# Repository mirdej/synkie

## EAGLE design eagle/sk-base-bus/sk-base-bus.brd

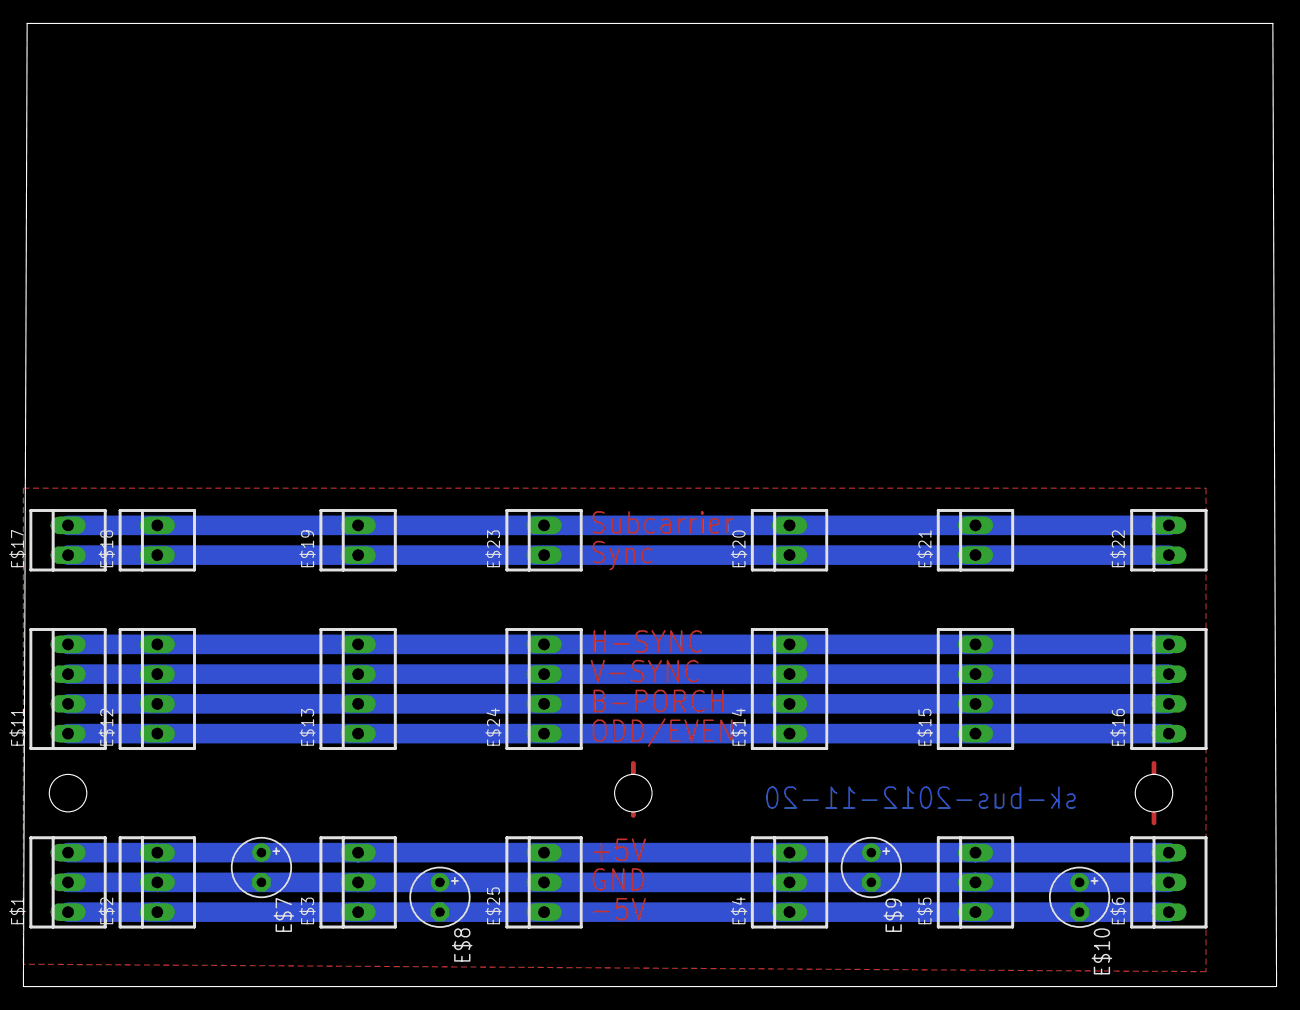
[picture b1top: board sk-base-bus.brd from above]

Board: 2 copper layers, 107.0 x 82.2 mm, 25 parts (0 on the bottom side), 9 nets.

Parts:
E$1, E$2, E$3, E$4, E$5, E$6, E$25: 22-23-2031
E$7, E$8, E$9, E$10: E2,5-5
E$11, E$12, E$13, E$14, E$15, E$16, E$24: 22-23-2041
E$17, E$18, E$19, E$20, E$21, E$22, E$23: 22-23-2021

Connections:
AGND: E$17.2, E$18.2, E$19.2, E$20.2, E$21.2, E$22.2
GND: E$1.2, E$2.2, E$3.2, E$4.2, E$5.2, E$6.2
S$1: E$1.3, E$2.3, E$3.3, E$4.3, E$5.3, E$6.3
S$3: E$1.1, E$2.1, E$3.1, E$4.1, E$5.1, E$6.1
S$5: E$11.4, E$12.4, E$13.4, E$14.4, E$15.4, E$16.4
S$6: E$11.3, E$12.3, E$13.3, E$14.3, E$15.3, E$16.3
S$7: E$11.2, E$12.2, E$13.2, E$14.2, E$15.2, E$16.2
S$8: E$11.1, E$12.1, E$13.1, E$14.1, E$15.1, E$16.1
S$10: E$17.1, E$18.1, E$19.1, E$20.1, E$21.1, E$22.1

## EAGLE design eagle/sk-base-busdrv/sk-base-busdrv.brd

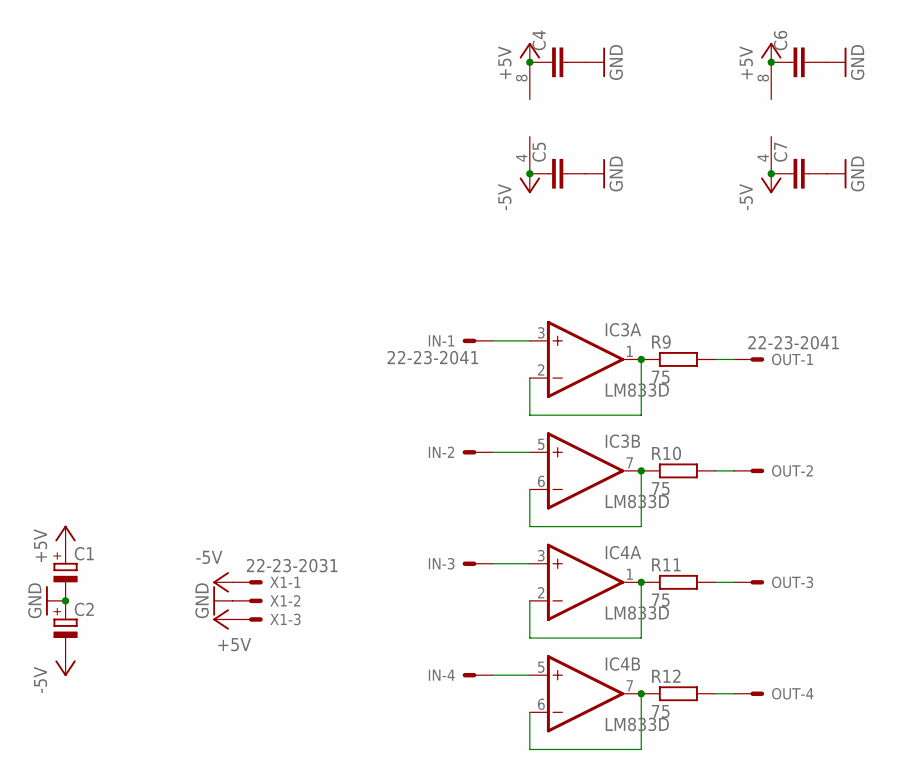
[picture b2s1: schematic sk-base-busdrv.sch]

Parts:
C1, C2: CPOL-EUCT6032; CT6032
C4, C5, C6, C7: C-EUC1206; C1206
IC3, IC4: LM833D; SO08
IN: 22-23-2041
OUT: 22-23-2041
R9, R10, R11, R12: 75; R1206
X1: 22-23-2031

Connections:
+5V: C1.+, C4.1, C6.1, IC3.8 (V+), IC4.8 (V+), X1.3
-5V: C2.-, C5.1, C7.1, IC3.4 (V-), IC4.4 (V-), X1.1
GND: C1.-, C2.+, C4.2, C5.2, C6.2, C7.2, X1.2
unnamed: OUT.1, R9.2
unnamed: OUT.2, R10.2
unnamed: OUT.3, R11.2
unnamed: OUT.4, R12.2
unnamed: IC4.5 (+IN), IN.4
unnamed: IC4.3 (+IN), IN.3
unnamed: IC3.5 (+IN), IN.2
unnamed: IC3.3 (+IN), IN.1
unnamed: IC3.1 (OUT), IC3.2 (-IN), R9.1
unnamed: IC3.6 (-IN), IC3.7 (OUT), R10.1
unnamed: IC4.1 (OUT), IC4.2 (-IN), R11.1
unnamed: IC4.6 (-IN), IC4.7 (OUT), R12.1

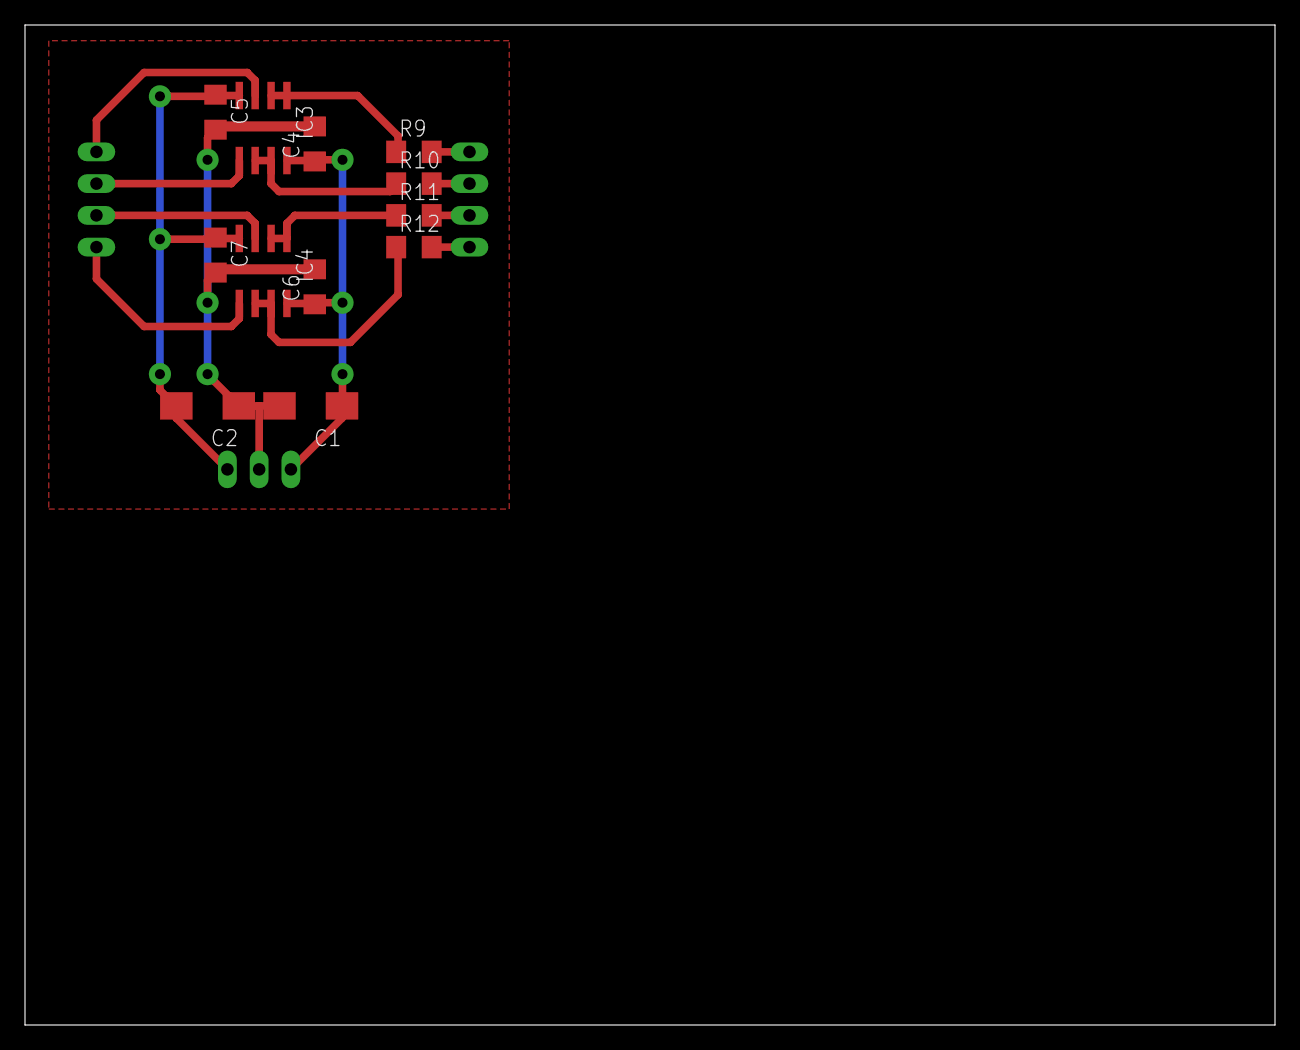
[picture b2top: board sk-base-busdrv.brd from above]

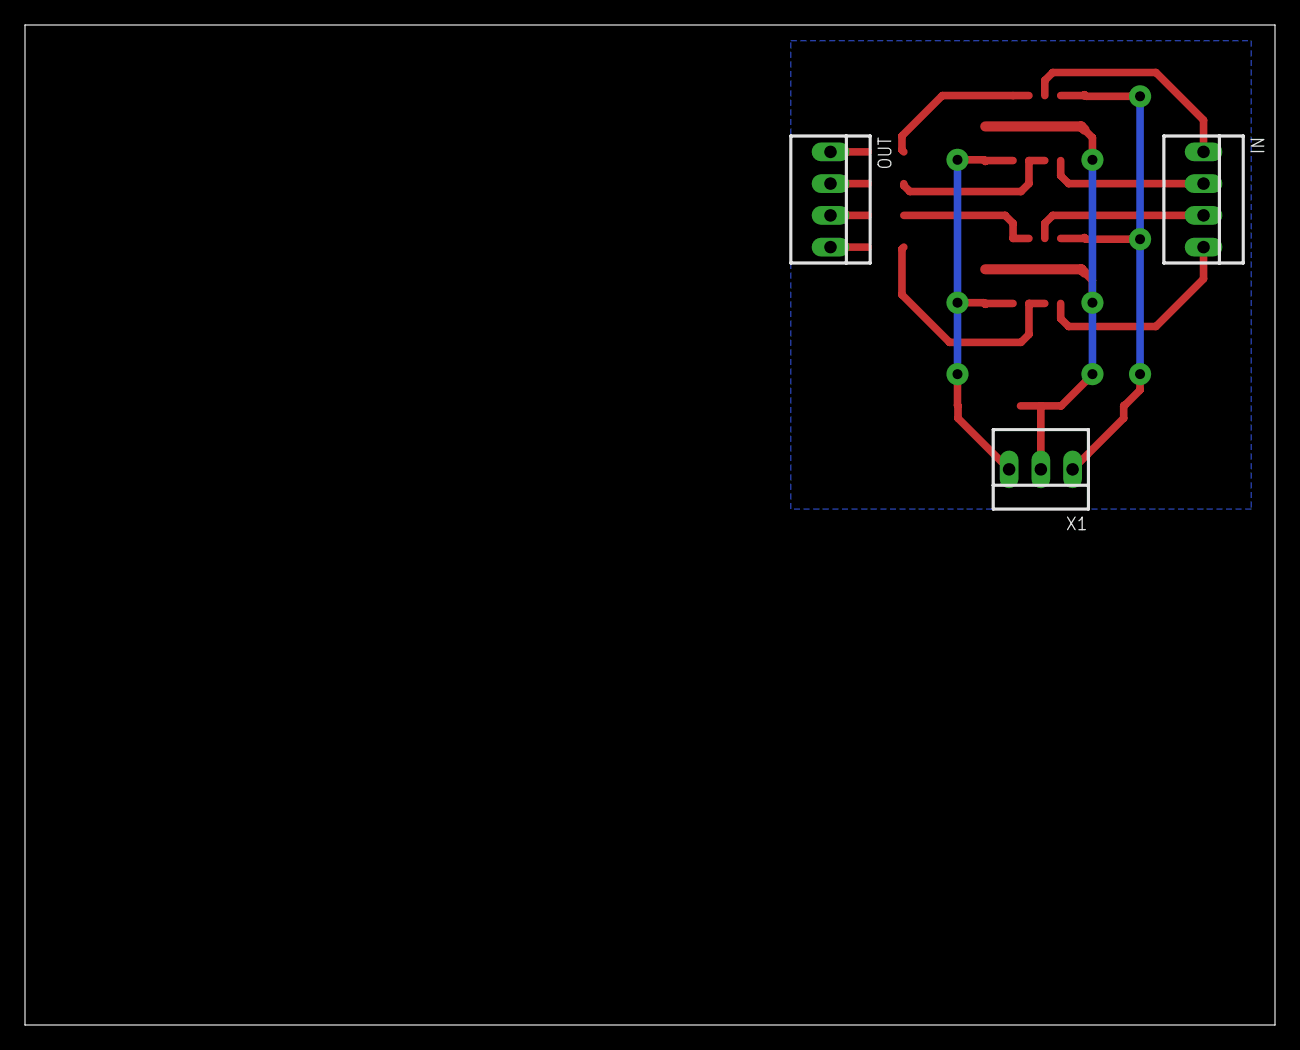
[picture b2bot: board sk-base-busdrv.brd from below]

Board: 2 copper layers, 100.0 x 80.0 mm, 15 parts (3 on the bottom side), 15 nets.

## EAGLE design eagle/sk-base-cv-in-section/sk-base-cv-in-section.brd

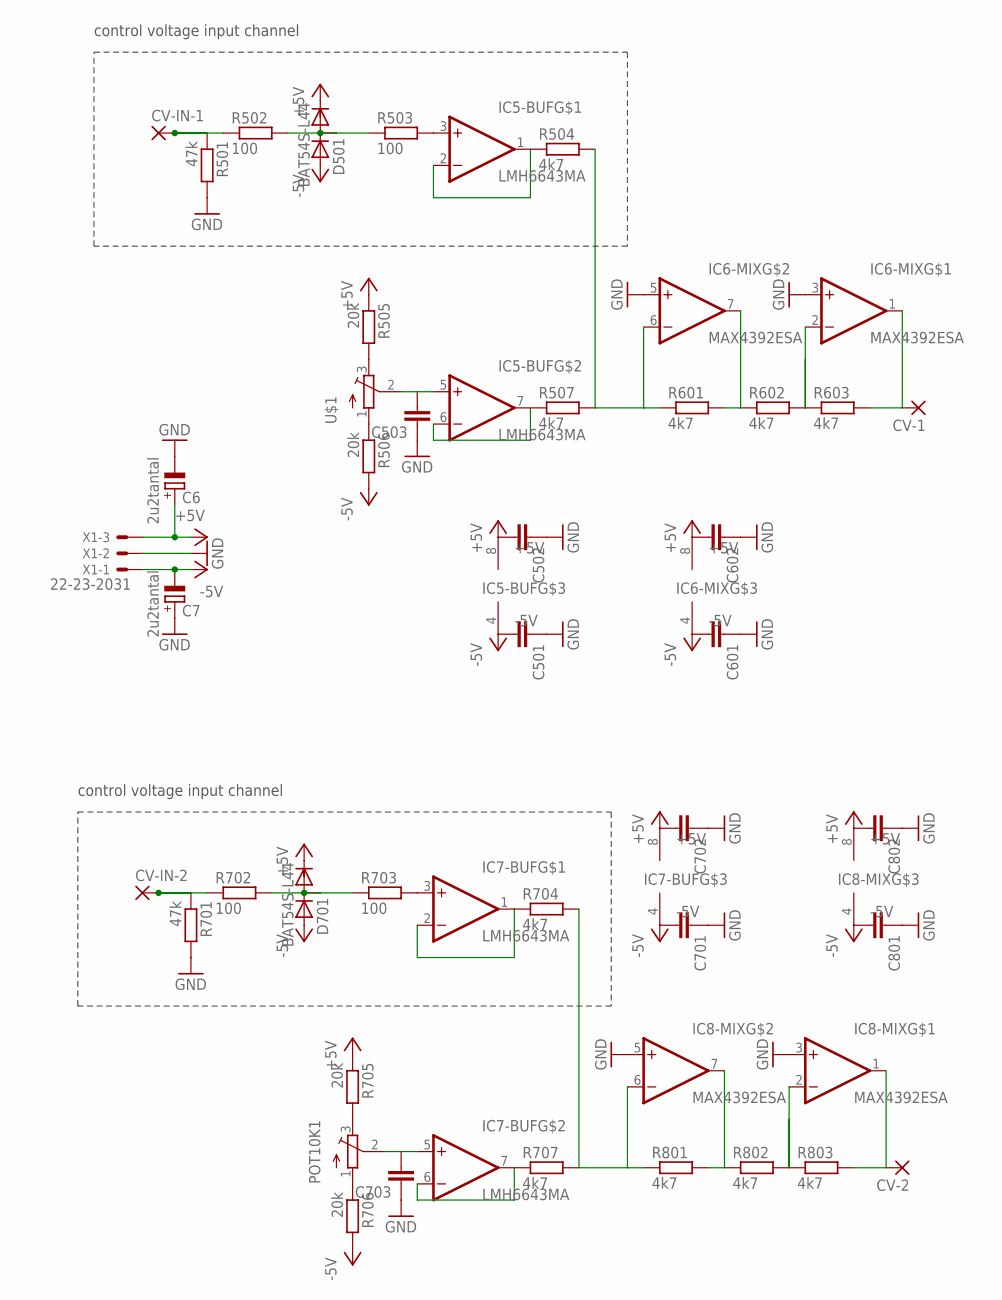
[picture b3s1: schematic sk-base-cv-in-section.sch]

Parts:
C6, C7: 2u2tantal; CT3528
C501, C502, C503, C601, C602, C701, C702, C703, C801, C802: C-EUC1206; C1206
CV-1, CV-2: 3,17/1,1
CV-IN-1, CV-IN-2: 3,17/1,1
D501, D701: BAT54S-L44; SOT23
IC5-BUF, IC7-BUF: LMH6643MA; SO08
IC6-MIX, IC8-MIX: MAX4392ESA; SO08
POT10K1: 10k; ALPS_RK09L1120
R501, R701: 47k; R1206
R502, R503, R702, R703: 100; R1206
R504, R507, R601, R602, R603, R704, R707, R801, R802, R803: 4k7; R1206
R505, R506, R705, R706: 20k; R1206
U$1: ALPS_RK09K111_H09L1120; ALPS_RK09L1120
X1: 22-23-2031

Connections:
+5V: C6.+, C502.2, C602.2, C702.2, C802.2, D501.2 (C), D701.2 (C), IC5-BUF.8 (+5V), IC6-MIX.8 (+5V), IC7-BUF.8 (+5V), IC8-MIX.8 (+5V), R505.1, R705.1, X1.3
-5V: C7.-, C501.2, C601.2, C701.2, C801.2, D501.1 (A), D701.1 (A), IC5-BUF.4 (-5V), IC6-MIX.4 (-5V), IC7-BUF.4 (-5V), IC8-MIX.4 (-5V), R506.2, R706.2, X1.1
GND: C6.-, C7.+, C501.1, C502.1, C503.1, C601.1, C602.1, C701.1, C702.1, C703.1, C801.1, C802.1, IC6-MIX.3 (+IN), IC6-MIX.5 (+IN), IC8-MIX.3 (+IN), IC8-MIX.5 (+IN), R501.2, R701.2, X1.2
unnamed: C503.2, IC5-BUF.5 (+IN), U$1.2 (W)
unnamed: R506.1, U$1.1 (S)
unnamed: R505.2, U$1.3 (E)
unnamed: CV-IN-1.1, R501.1, R502.1
unnamed: D501.3 (AC), R502.2, R503.1
unnamed: IC5-BUF.6 (-IN), IC5-BUF.7 (OUT), R507.1
unnamed: IC5-BUF.3 (+IN), R503.2
unnamed: IC5-BUF.1 (OUT), IC5-BUF.2 (-IN), R504.1
unnamed: IC6-MIX.6 (-IN), R504.2, R507.2, R601.1
unnamed: IC6-MIX.7 (OUT), R601.2, R602.1
unnamed: IC6-MIX.2 (-IN), R602.2, R603.1
unnamed: CV-1.1, IC6-MIX.1 (OUT), R603.2
unnamed: CV-IN-2.1, R701.1, R702.1
unnamed: D701.3 (AC), R702.2, R703.1
unnamed: IC7-BUF.3 (+IN), R703.2
unnamed: IC7-BUF.1 (OUT), IC7-BUF.2 (-IN), R704.1
unnamed: IC7-BUF.6 (-IN), IC7-BUF.7 (OUT), R707.1
unnamed: IC8-MIX.6 (-IN), R704.2, R707.2, R801.1
unnamed: IC8-MIX.7 (OUT), R801.2, R802.1
unnamed: IC8-MIX.2 (-IN), R802.2, R803.1
unnamed: CV-2.1, IC8-MIX.1 (OUT), R803.2
unnamed: C703.2, IC7-BUF.5 (+IN), POT10K1.2 (W)
unnamed: POT10K1.1 (S), R706.1
unnamed: POT10K1.3 (E), R705.2

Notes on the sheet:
control voltage input channel

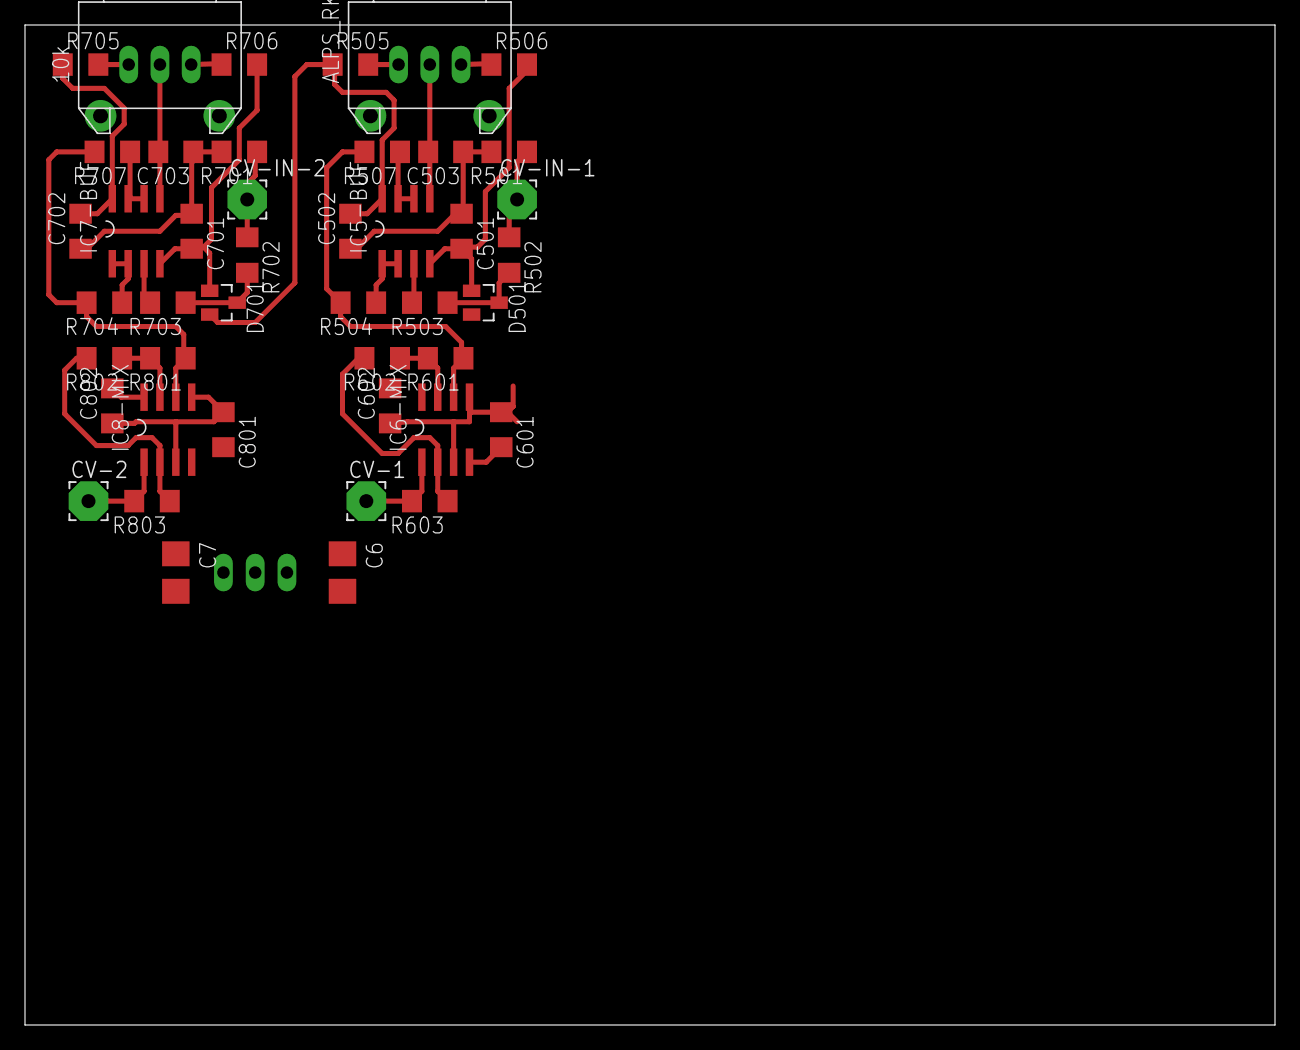
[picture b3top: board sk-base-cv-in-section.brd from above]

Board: 2 copper layers, 100.0 x 80.0 mm, 45 parts (1 on the bottom side), 27 nets.

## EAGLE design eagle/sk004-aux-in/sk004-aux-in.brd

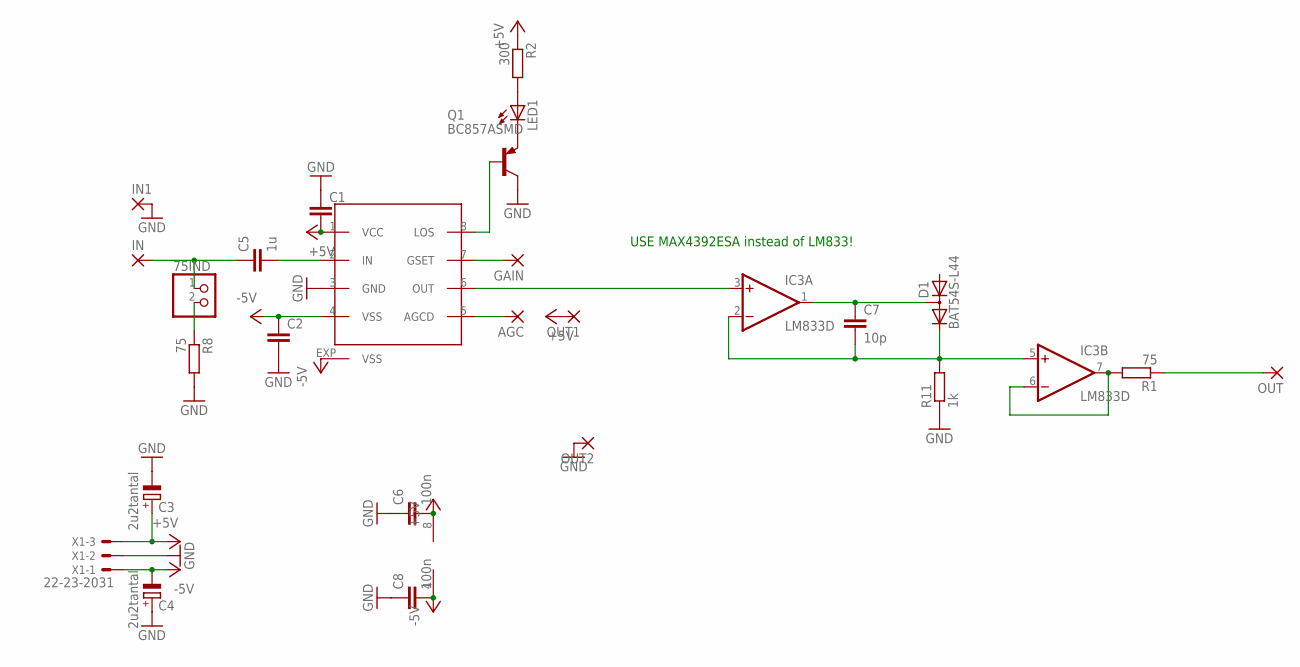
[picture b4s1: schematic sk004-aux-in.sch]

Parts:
75IND: PINHD-1X2; 1X02
AGC: 2,54/1,0
C1, C2: C-EUC1206; C1206
C3, C4: 2u2tantal; CT3528
C5: 1u; C1206
C6, C8: 100n; C1206
C7: 10p; C1206
D1: BAT54S-L44; SOT23
GAIN: 2,54/1,0
IC3: LM833D; SO08
IN, IN1: 3,17/1,1
LED1: LED3MM
OUT, OUT1, OUT2: 3,17/1,1
Q1: BC857ASMD; SOT23-BEC
R1, R8: 75; R1206
R2: 300; R1206
R11: 1k; R1206
U$1: MAX7450; SO08-EXP
X1: 22-23-2031

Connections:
+5V: C1.2, C3.+, C6.2, IC3.8 (V+), OUT1.1, R2.1, U$1.1 (VCC), X1.3
-5V: C2.1, C4.-, C8.2, IC3.4 (V-), U$1.4 (VSS), U$1.EXP (VSS), X1.1
GND: C1.1, C2.2, C3.-, C4.+, C6.1, C8.1, IN1.1, OUT2.1, Q1.C, R8.2, R11.1, U$1.3 (GND), X1.2
unnamed: 75IND.2, R8.1
unnamed: 75IND.1, C5.1, IN.1
unnamed: IC3.3 (+IN), U$1.6 (OUT)
unnamed: GAIN.1, U$1.7 (GSET)
unnamed: AGC.1, U$1.5 (AGCD)
unnamed: LED1.A, R2.2
unnamed: Q1.B, U$1.8 (LOS)
unnamed: C5.2, U$1.2 (IN)
unnamed: LED1.K (C), Q1.E
unnamed: IC3.6 (-IN), IC3.7 (OUT), R1.2
unnamed: OUT.1, R1.1
unnamed: C7.1, D1.3 (AC), IC3.1 (OUT)
unnamed: C7.2, D1.2 (C), IC3.2 (-IN), IC3.5 (+IN), R11.2

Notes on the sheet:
USE MAX4392ESA instead of LM833!

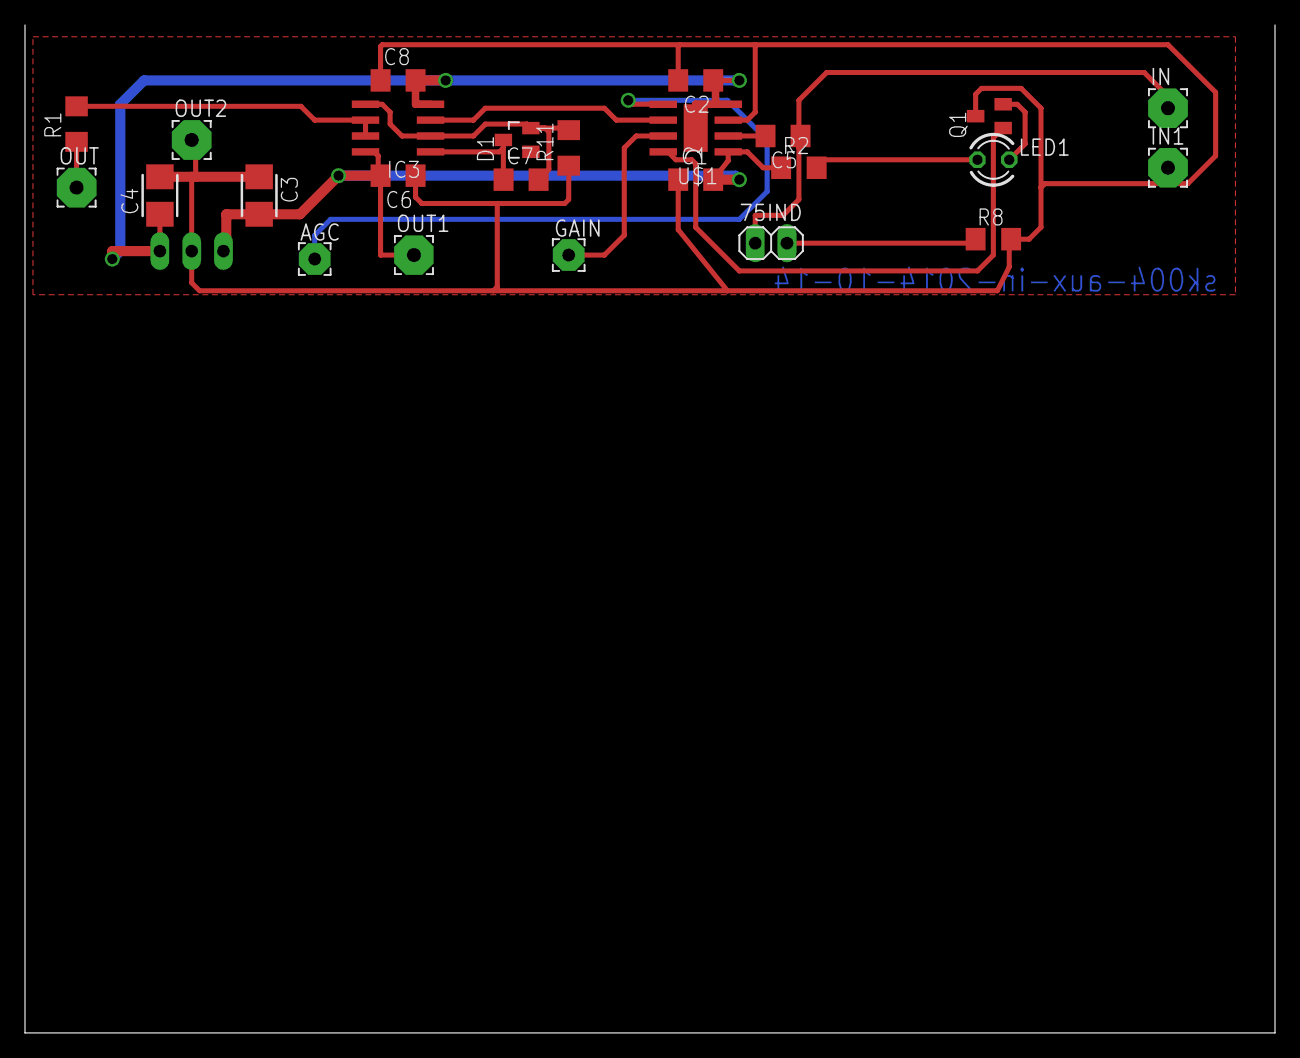
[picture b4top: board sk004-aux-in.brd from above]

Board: 2 copper layers, 100.0 x 80.6 mm, 26 parts (1 on the bottom side), 16 nets.

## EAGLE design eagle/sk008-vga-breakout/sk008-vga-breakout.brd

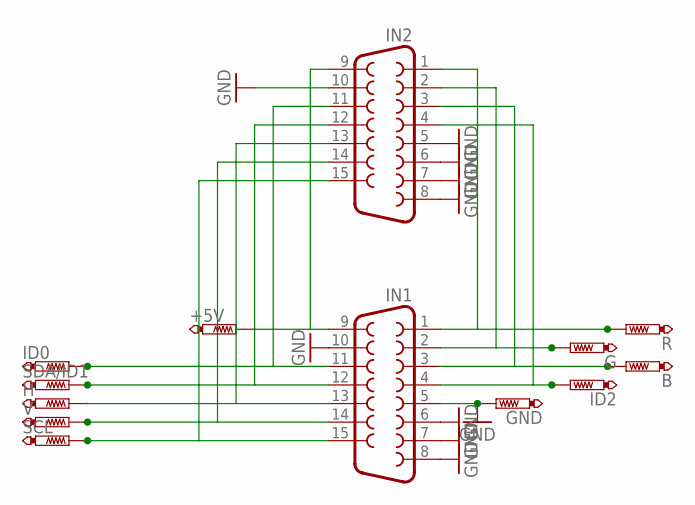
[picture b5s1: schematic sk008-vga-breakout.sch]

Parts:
+5V: PTR1PAD1-17Y; P1-17Y
B: PTR1PAD1-17Y; P1-17Y
G: PTR1PAD1-17Y; P1-17Y
GND: PTR1PAD1-17Y; P1-17Y
H: PTR1PAD1-17Y; P1-17Y
ID0, ID2: PTR1PAD1-17Y; P1-17Y
IN1, IN2: F15HDH; HDF15H
R: PTR1PAD1-17Y; P1-17Y
SCL: PTR1PAD1-17Y; P1-17Y
SDA/ID1: PTR1PAD1-17Y; P1-17Y
V: PTR1PAD1-17Y; P1-17Y

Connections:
GND: GND.TP, IN1.5, IN1.6, IN1.7, IN1.8, IN1.10, IN2.5, IN2.6, IN2.7, IN2.8, IN2.10
unnamed: IN1.1, IN2.1, R.TP
unnamed: G.TP, IN1.2, IN2.2
unnamed: B.TP, IN1.3, IN2.3
unnamed: H.TP, IN1.13, IN2.13
unnamed: IN1.12, IN2.12, SDA/ID1.TP
unnamed: IN1.14, IN2.14, V.TP
unnamed: IN1.15, IN2.15, SCL.TP
unnamed: +5V.TP, IN1.9, IN2.9
unnamed: ID2.TP, IN1.4, IN2.4
unnamed: ID0.TP, IN1.11, IN2.11

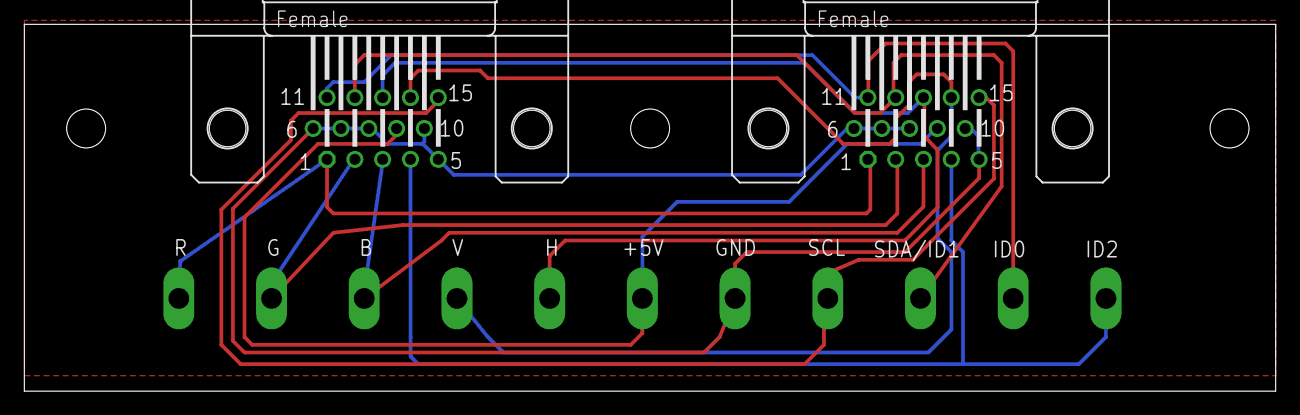
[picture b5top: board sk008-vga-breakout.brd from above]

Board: 2 copper layers, 102.8 x 30.2 mm, 13 parts (0 on the bottom side), 11 nets.

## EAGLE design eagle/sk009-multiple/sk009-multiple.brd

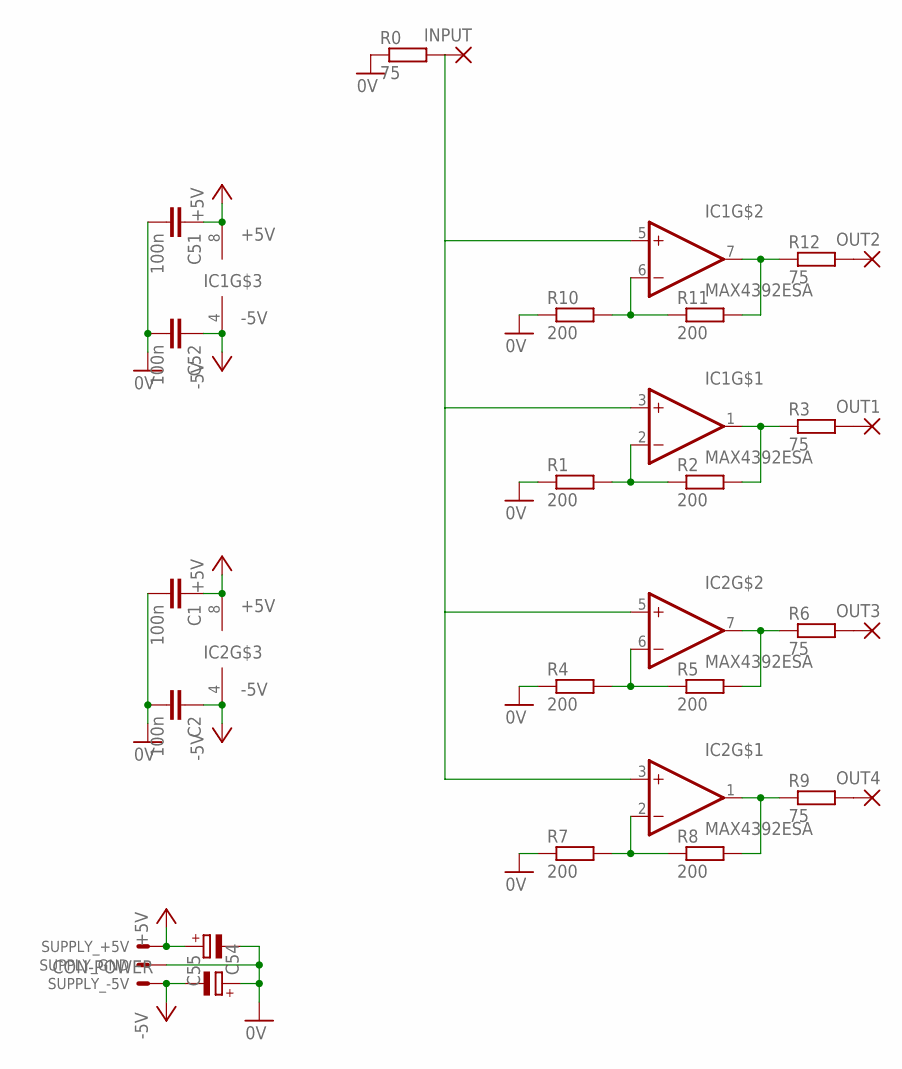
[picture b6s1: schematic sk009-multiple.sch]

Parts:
C1, C2, C51, C52: 100n; C0805
C54, C55: CPOL-EUCT3528; CT3528
IC1, IC2: MAX4392ESA; SO08
INPUT: 3,17/1,1
OUT1, OUT2, OUT3, OUT4: 3,17/1,1
R0, R3, R6, R9, R12: 75; R0805
R1, R2, R4, R5, R7, R8, R10, R11: 200; R0805
SUPPLY: CON-POWER; 22-23-2031

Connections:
0V: C1.2, C2.2, C51.2, C52.2, C54.+, C55.-, R0.1, R1.1, R4.1, R7.1, R10.1, SUPPLY.2
+5V: C1.1, C51.1, C55.+, IC1.8 (+5V), IC2.8 (+5V), SUPPLY.3
-5V: C2.1, C52.1, C54.-, IC1.4 (-5V), IC2.4 (-5V), SUPPLY.1
unnamed: IC1.2 (-IN), R1.2, R2.1
unnamed: IC1.1 (OUT), R2.2, R3.1
unnamed: OUT1.1, R3.2
unnamed: IC2.6 (-IN), R4.2, R5.1
unnamed: IC2.7 (OUT), R5.2, R6.1
unnamed: OUT3.1, R6.2
unnamed: IC2.2 (-IN), R7.2, R8.1
unnamed: IC2.1 (OUT), R8.2, R9.1
unnamed: OUT4.1, R9.2
unnamed: IC1.3 (+IN), IC1.5 (+IN), IC2.3 (+IN), IC2.5 (+IN), INPUT.1, R0.2
unnamed: IC1.6 (-IN), R10.2, R11.1
unnamed: IC1.7 (OUT), R11.2, R12.1
unnamed: OUT2.1, R12.2

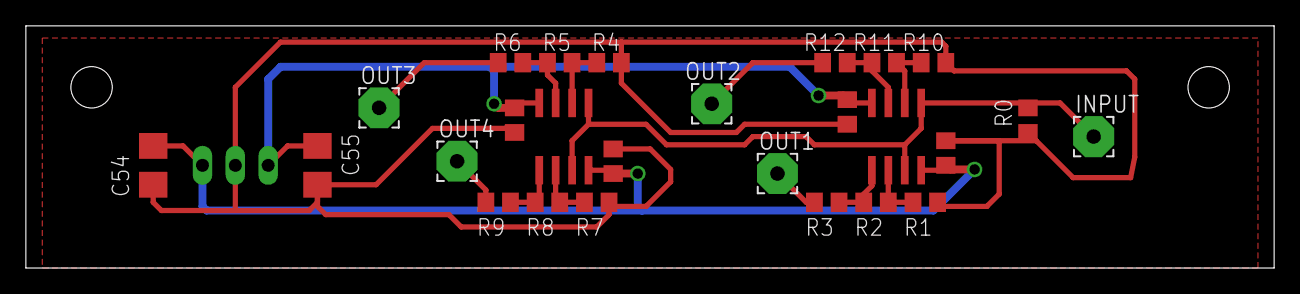
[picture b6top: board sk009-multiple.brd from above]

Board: 2 copper layers, 96.5 x 18.7 mm, 27 parts (1 on the bottom side), 16 nets.

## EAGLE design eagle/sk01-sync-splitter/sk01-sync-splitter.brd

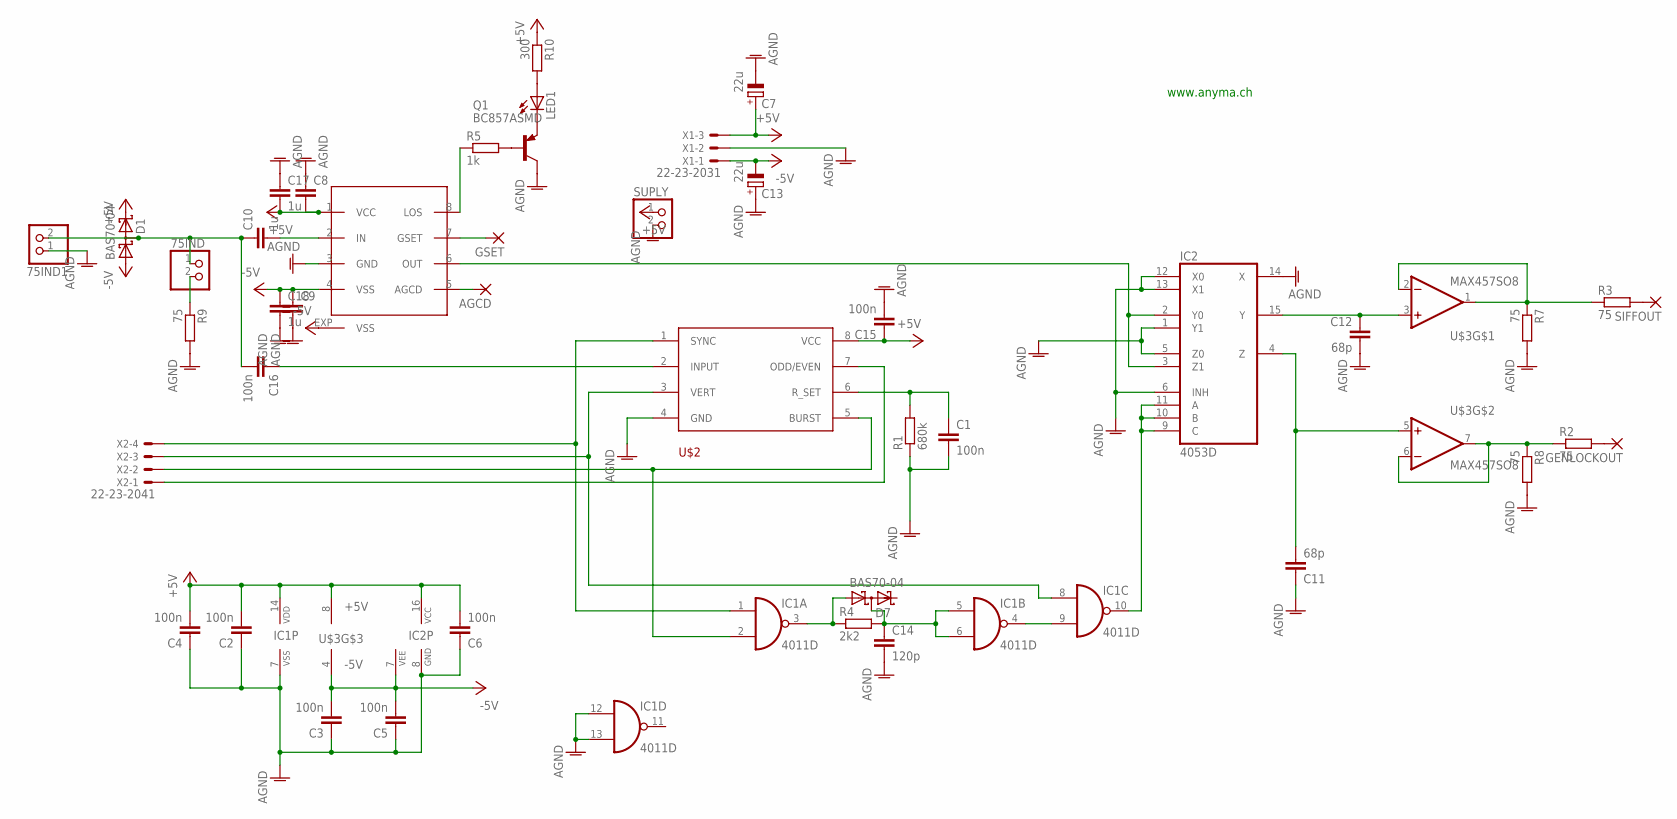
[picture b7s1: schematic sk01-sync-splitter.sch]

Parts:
75IND, 75IND1: PINHD-1X2; 1X02
AGCD: 3,17/1,1
C1, C2, C16: 100n; C1206
C3, C4, C5, C6, C15: 100n; C0805
C7, C13: 22u; CT3528
C8, C9: C-EUC0805; C0805
C10: 1u; C1206
C11, C12: 68p; C1206
C14: 120p; C1206
C17, C18: 1u; C0805
D1, D7: BAS70-04; SOT23
GENLOCKOUT: 3,17/1,1
GSET: 3,17/1,1
IC1: 4011D; SO14
IC2: 4053D; SO16
LED1: LED3MM
Q1: BC857ASMD; SOT23-BEC
R1: 680k; R1206
R2, R3, R7, R8, R9: 75; R1206
R4: 2k2; R1206
R5: 1k; R1206
R10: 300; R1206
SIFFOUT: 3,17/1,1
SUPLY: PINHD-1X2; 1X02
U$2: LM1881; SO08
U$3: MAX457SO8; SO08
U$4: MAX7450; SO08-EXP
X1: 22-23-2031
X2: 22-23-2041

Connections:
+5V: C2.2, C4.2, C6.2, C7.+, C8.2, C15.1, C17.2, D1.2 (C2), IC1.14 (VDD), IC2.16 (VCC), R10.1, SUPLY.1, U$2.8 (VCC), U$3.8 (+5V), U$4.1 (VCC), X1.3
-5V: C3.2, C5.2, C9.1, C13.-, C18.1, D1.1 (A1), IC2.7 (VEE), U$3.4 (-5V), U$4.4 (VSS), U$4.EXP (VSS), X1.1
AGND: 75IND1.1, C1.2, C2.1, C3.1, C4.1, C5.1, C6.1, C7.-, C8.1, C9.2, C11.1, C12.2, C13.+, C14.2, C15.2, C17.1, C18.2, IC1.7 (VSS), IC1.12 (I0), IC1.13 (I1), IC2.1 (Y1), IC2.5 (Z0), IC2.6 (INH), IC2.8 (GND), IC2.12 (X0), IC2.13 (X1), IC2.14 (X), Q1.C, R1.1, R7.2, R8.2, R9.2, SUPLY.2, U$2.4 (GND), U$4.3 (GND), X1.2
CTL: IC1.10 (O), IC2.9 (C), IC2.10 (B), IC2.11 (A)
unnamed: IC1.1 (I0), U$2.1 (SYNC), X2.4
unnamed: LED1.A, R10.2
unnamed: IC1.2 (I1), U$2.5 (BURST), X2.2
unnamed: U$2.7 (ODD/EVEN), X2.1
unnamed: LED1.K (C), Q1.E
unnamed: C1.1, R1.2, U$2.6 (R_SET)
unnamed: Q1.B, R5.2
unnamed: 75IND.2, R9.1
unnamed: IC1.4 (O), IC1.9 (I1)
unnamed: C11.2, IC2.4 (Z), U$3.5 (+IN)
unnamed: C10.2, U$4.2 (IN)
unnamed: R3.2, SIFFOUT.1
unnamed: R2.1, R8.1, U$3.6 (-IN), U$3.7 (OUT)
unnamed: IC2.2 (Y0), IC2.3 (Z1), U$4.6 (OUT)
unnamed: R3.1, R7.1, U$3.1 (OUT), U$3.2 (-IN)
unnamed: C12.1, IC2.15 (Y), U$3.3 (+IN)
unnamed: IC1.8 (I0), U$2.3 (VERT), X2.3
unnamed: 75IND.1, 75IND1.2, C10.1, C16.2, D1.3 (C1A2)
unnamed: GSET.1, U$4.7 (GSET)
unnamed: C14.1, D7.3 (C1A2), IC1.5 (I0), IC1.6 (I1), R4.2
unnamed: GENLOCKOUT.1, R2.2
unnamed: D7.1 (A1), IC1.3 (O), R4.1
unnamed: R5.1, U$4.8 (LOS)
unnamed: C16.1, U$2.2 (INPUT)
unnamed: AGCD.1, U$4.5 (AGCD)

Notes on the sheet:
www.anyma.ch

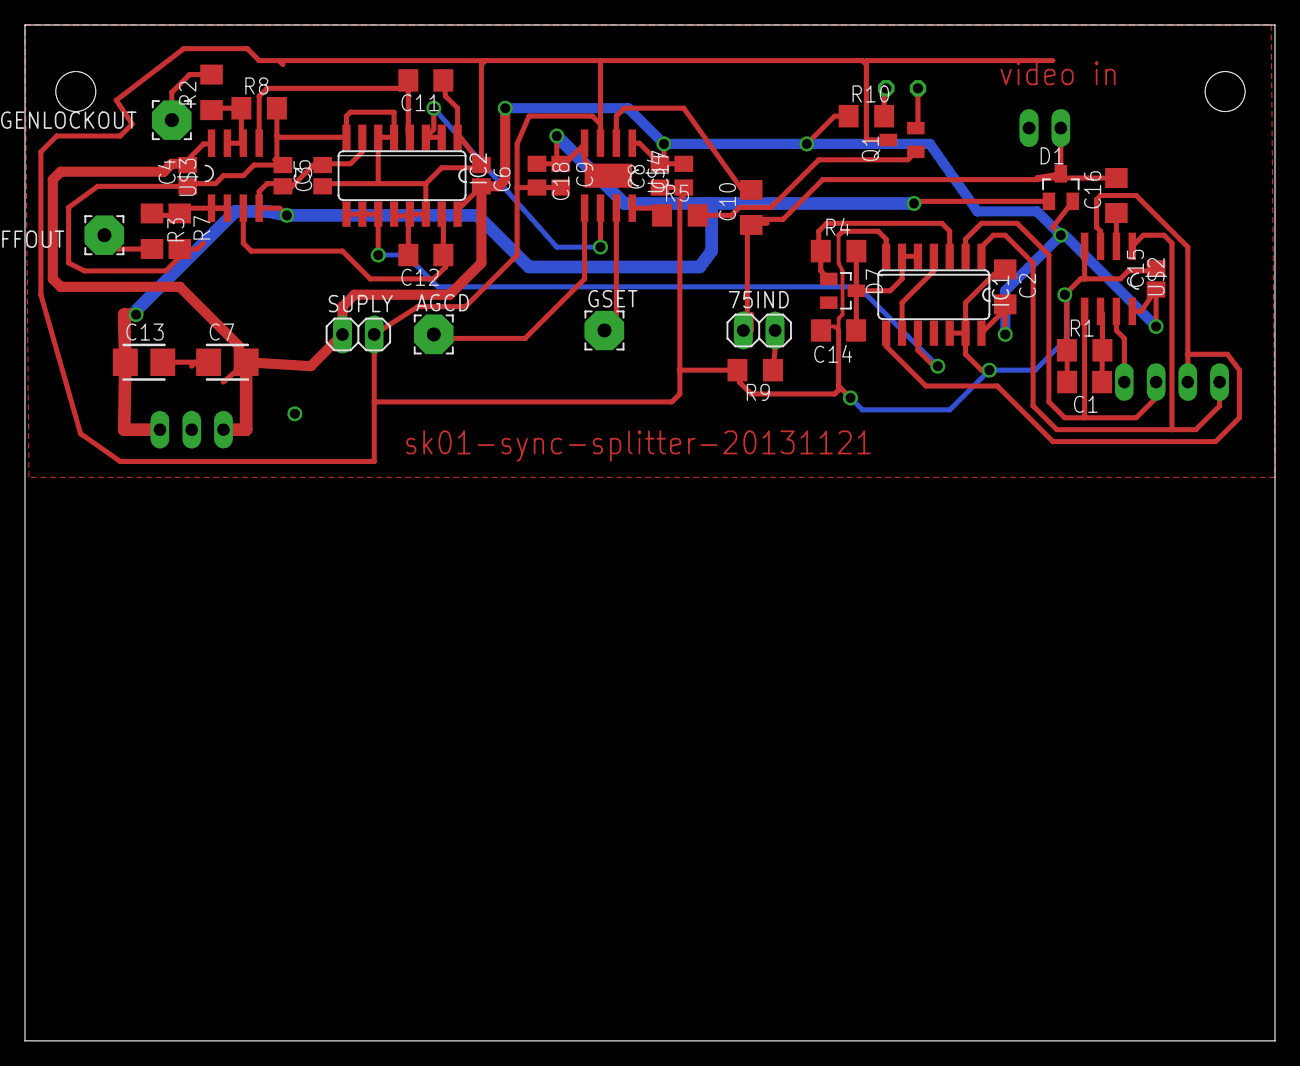
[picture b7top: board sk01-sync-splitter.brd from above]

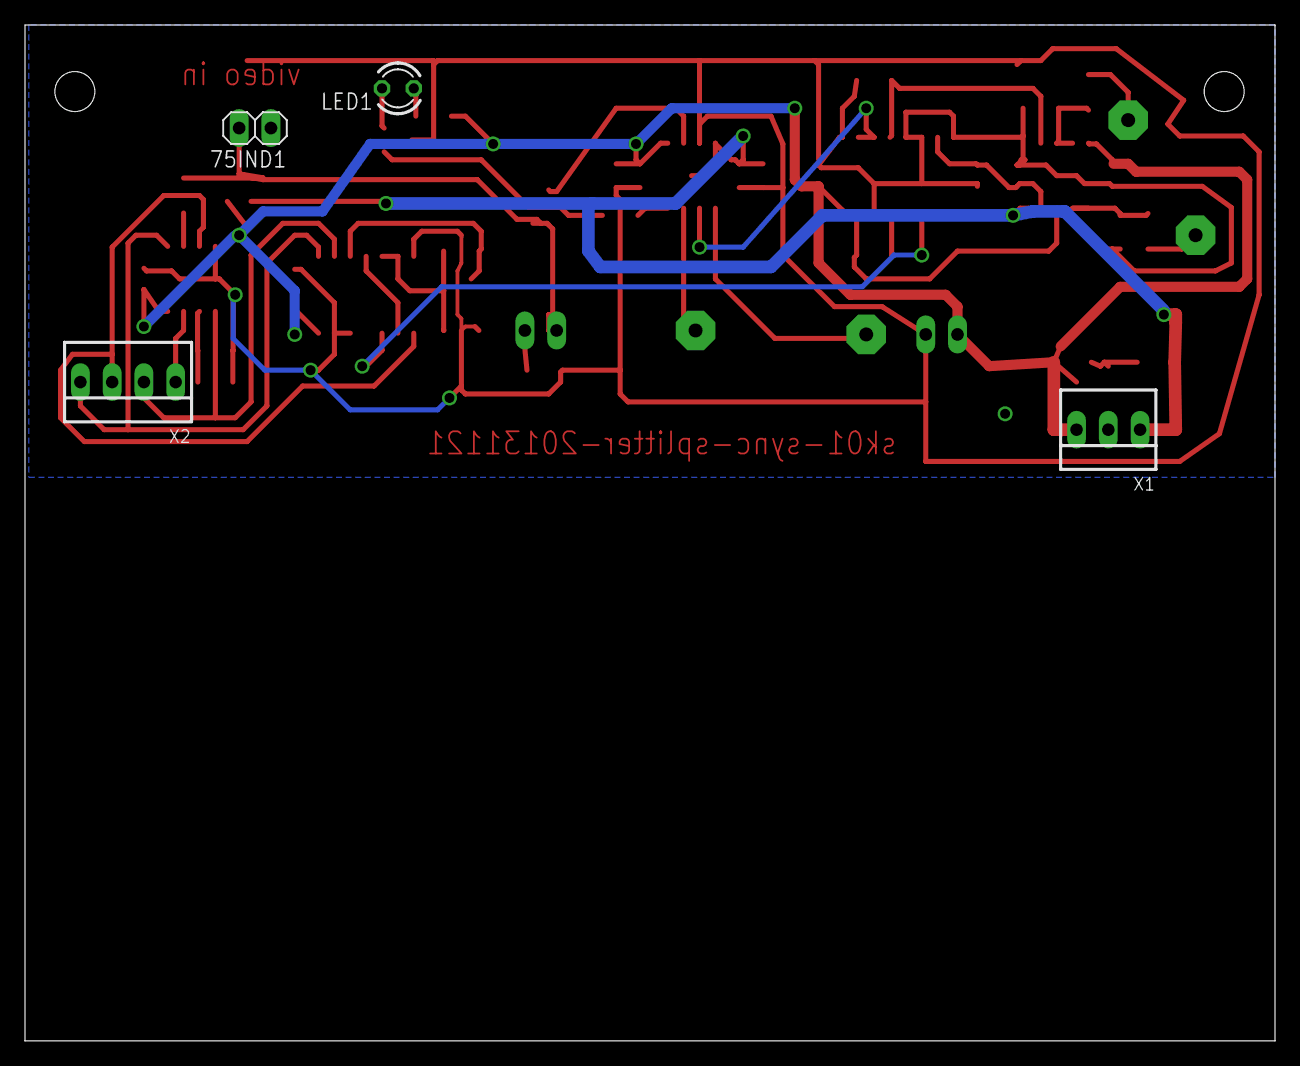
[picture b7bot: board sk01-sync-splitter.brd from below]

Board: 2 copper layers, 100.0 x 81.3 mm, 45 parts (4 on the bottom side), 29 nets.
